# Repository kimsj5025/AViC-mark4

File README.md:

# AViC mark4

이번에는 기존과는 다르게 완전 하이엔드급 보드를 제작해 보려고 하였다. 이를 위해서 TDK사의 가장 최신 센서와 20cm정확도를 갖는 기압 센서, 그리고 내장 GPS와 지자기 센서, 총 4개의 pyro까지, 필요한 모든 것들을 신용카드 사이즈의 보드 안에 통합하려고 하였다.

# 기능 테스트

- [x]  USB 업로드 테스트
- [x]  LED테스트
- [x]  I2C 스캔
- [x]  SDMMC 테스트
- [x]  wifi
- [x]  Pyro 테스트
- [x]  부저
- [x]  GNSS
- [x]  5v out
- [ ]  외부 배터리 연결시 전원 역류방지

## MPU

이번에는 풀 사이즈 Esp32 S3 wroom 1 가 아니라 esp32 s3 mini를 사용하였다.

주요 사양으로는 

- **프로세서:** Xtensa® 32비트 LX7 듀얼 코어 프로세서
- **클럭 주파수:** 최대 240 MHz
- **무선 통신:**
    - 2.4GHz Wi-Fi (802.11 b/g/n)
    - Bluetooth 5 (LE)
- **메모리:**
    - 내부 SRAM: 512KB

주요 사양은 기존의 [AViCDEsp32](https://www.notion.so/AViCDEsp32-20f2a69ddfde80878ec1d9f6c206afdb?pvs=21) 에 사용되었던 MPU와 같은 성능이다.

## 가속도계

가속도계는 TDK InvenSense사의 ICM-45686 6축 가속도 센서를 사용하였다. 이 센서는 최대 32g까지 측정할 수 있으며, 해상도는 16bit이다. 흔히 아두이노용 가속도계로 알려진 mpu6050를 만든 회사의 최신 플래그쉽 가속도 센서이다.

## 기압계

기압계는 MS5607을 사용하였다. 

이 센서의 분해능은 20cm 정도의 높이를 측정할 수 있다. 이 정도면 꽤 정확한 기압계라고 볼 수 있다.

## 자자기계

이번에는 자이로 센서의 드리프트를 보정하기 위해 LIS2MDL 3축 지자기계를 사용하였다.

## GPS

저번 보드에서는 GPS신호를 받으려면 외장 모듈을 활용해야 했지만, 이번에는 ATGM336h과 U.FL 컨넥터로 안테나만 연결해주면 GPS신호를 바로 보드에서 받을 수 있게 하였다.

또한 LED를 연결해 PPS(1초에 한번 신호를 보내는 핀)을 통해 연결 여부를 시각적으로 볼 수 있도록 해 주었다.

## Micro SD카드

저번과 같이 SDMMC를 위한 SD카드 슬롯도 배치하여 주었다.

## 모스펫 스위치

이번에는 4개의 파이로 체널로 구성되었는데. 듀얼 N타입 모스펫이 두개 들어가 있다. 각각의 배선에 따라 최대 4A의 전류를 흐르게 할 수 있다.

## 3.3V, 5V출력

저번과 같이 레귤레이터로는 AMS1117을 사용했다. 다른 점이라면 이번에는 3.3V뿐 아니라 5V도 지원이 된다는 것이다. 이는 추후 사용할 카메라인 Runcam Split 4 4k가 최소 5V 입력을 지원하기에, 이를 보드 내에서 처리하기 위함이다.

## LED 인디케이터

저번 보드에서의 문제점이 이게 작동 중인지 아닌지 관계 없이 전원이 들어오면 LED가 계속 켜져있는다는 것이였는데, 이를 해결하기 위해 MPU에서 직접 이를 조정하게 해 이 문제를 해결했다.

웹에서 센서 데이터를 읽어올 때 마다 LED가 깜빡이게 만든 모습

## 부저

이 는 원래 에이비오닉스로 활용될 계획도 갖고 있어서, 로켓 내부에 있을 때에 청각적으로 작동중임을 알 수 있도록 부저를 달아서 알 수 있게 하였다.

또한 부팅시에 부팅음을 넣어서 시리얼 모니터를 보지 않아도 정상적으로 리셋이 되었는지 알 수 있도록 하였다.

## USB-C

ESP32 s3는 풀 스피드 USB2.0를 지원하고 내장 CDC가 있기 때문에 D- D+핀만 정상적으로 연결해 준다면 usb를 이용하여 코딩과 시리얼 모니터(UART0)를 볼 수 있다. 또한 USB에서 나오는 5V전원을 통해 보드 전체의 전원이 들어올 수 있도록 해 주었다. 이를 통해 기존 코드 업로드 방식에서 엄청난 혁신을 이루었는데, 코드를 업로드 할 때마다 리셋 버튼을 누르는 수고와 항상 USB TTL컨버터를 찾아야 하는 번거로움에서 해방되었다. (그래서 USB TTL컨버터를 잃어버렸다;)

또한 이 USB-C에 대한 글을 하나 작성하였다. 

https://kimsj5025.tistory.com/entry/Esp32-S3-USB-OTG-%EC%8B%9C%EB%A6%AC%EC%96%BC-%EB%AA%A8%EB%8B%88%ED%84%B0%EA%B0%80-%EC%95%88%EB%82%98%EC%98%AC%EB%95%8C-%ED%95%B4%EA%B2%B0-%EB%B0%A9%EB%B2%95-ArduinoIDE-PlatformIO

## 더 많은 GPIO

PWM용, UART 통신(+ RX TX -)을 위한 헤더핀 총 8개 그리고 3.3,5V 각각 두개, 4개의 파이로 체널, 9개의 GPIO, 3개의 GND 총 20개의 터미널 블럭을 이용한 단자를 만들어 주었다. 또한 각가그이 M4 나사 규격의 마운트홀도 모두 GND에 연결해 주어 총 7개의 GND단자가 있게 되었다.

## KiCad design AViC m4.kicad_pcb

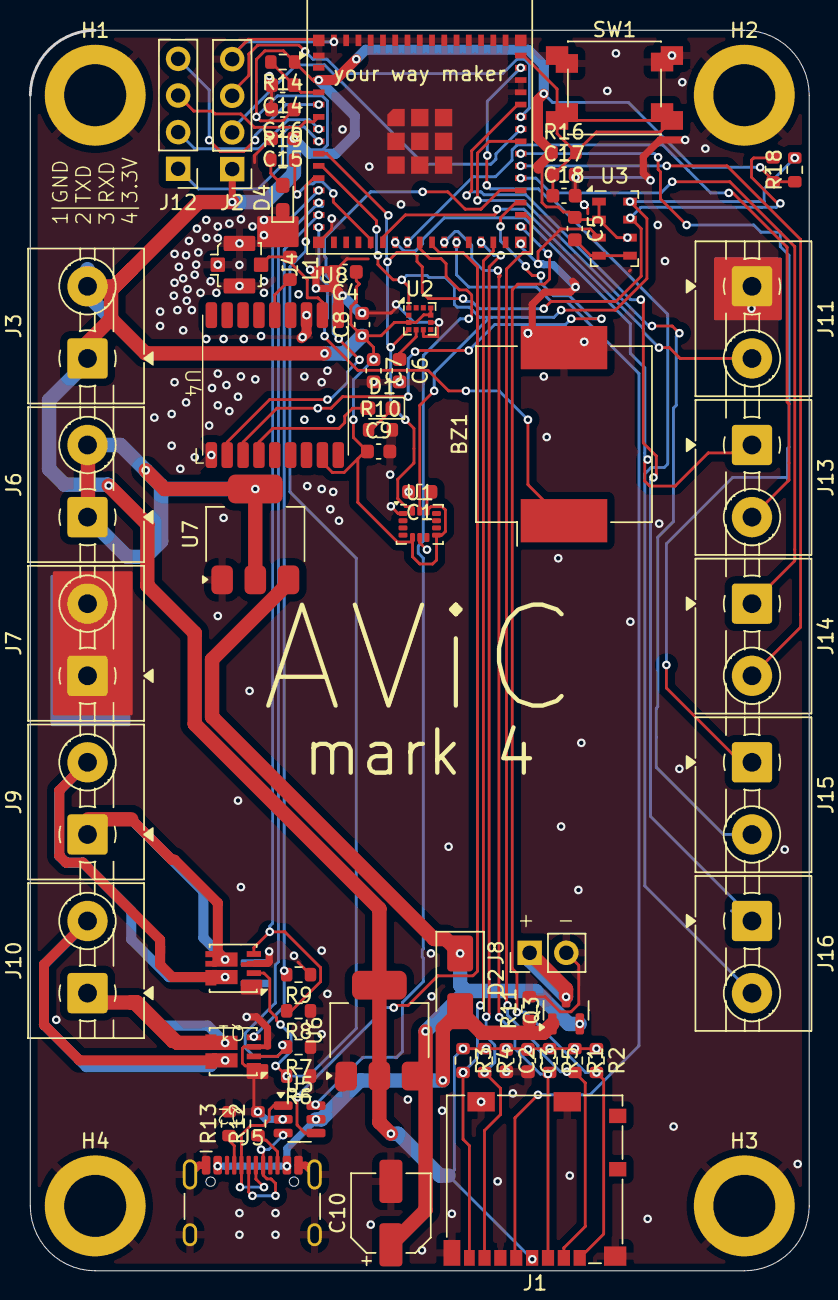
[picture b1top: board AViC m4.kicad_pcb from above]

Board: 2 copper layers, 54.0 x 86.0 mm, 70 parts (0 on the bottom side), 56 nets.

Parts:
BZ1: Buzzer; Buzzer_Mallory_AST1240MLQ
C1, C2, C4, C5, C7, C9, C16: 10uF; C_0603_1608Metric
C3, C8, C14, C15, C17: 0.1uF; C_0603_1608Metric
C6: 220nF; C_0603_1608Metric
C10: 47uF; CP_Elec_5x5.4
C18: 1uF; C_0603_1608Metric
D1: RED; LED_0603_1608Metric_Pad1.05x0.95mm_HandSolder
D2: SS14; D_SMA
D4: LED; LED_0603_1608Metric_Pad1.05x0.95mm_HandSolder
H1, H2, H3, H4: m4; MountingHole_4.3mm_M4_ISO14580_Pad
J1: Micro_SD_Card_Det_Hirose_DM3AT; microSD_HC_Molex_104031-0811
J2: Lora; PinHeader_1x04_P2.54mm_Vertical
J3, J6, J7, J9, J10: Power ternimal LEFT; TerminalBlock_MaiXu_MX126-5.0-02P_1x02_P5.00mm
J4: Conn_Coaxial; U.FL_Molex_MCRF_73412-0110_Vertical
J5: USB_C_Receptacle_USB2.0_16P; USB_C_Receptacle_HCTL_HC-TYPE-C-16P-01A
J8: Batt; PinHeader_1x02_P2.54mm_Vertical
J11, J13, J14, J15, J16: GPIOs; TerminalBlock_MaiXu_MX126-5.0-02P_1x02_P5.00mm
J12: PWM; PinHeader_1x04_P2.54mm_Vertical
L1: 27n; L_0603_1608Metric
Q1, Q2: SI7232DN-T1-GE3; mosfet_custom
Q3: DMG2302U; SOT-23
R1, R2, R3, R4, R5, R14, R16, R17, R18: 10k; R_0603_1608Metric
R6, R7, R8, R9: 4.7k; R_0603_1608Metric
R10: 1KR; R_0603_1608Metric
R11: 100k; R_0603_1608Metric
R12, R13: 5k1; R_0603_1608Metric
R19: 330; R_0603_1608Metric
SW1: Flash Mode; SW_SPST_PTS645
U1: ICM-45686; LGA-14_3x2.5mm_P0.5mm_LayoutBorder3x4y
U2: LIS2MDL; LGA-12_2x2mm_P0.5mm
U3: MS5607-02BA; LGA-8_3x5mm_P1.25mm
U4: ATGM336h
U5: USBLC6-2SC6; SOT-23-6
U6: AMS1117-3.3; SOT-223-3_TabPin2
U7: AMS1117-5.0; SOT-223-3_TabPin2
U8: ESP32-S3-MINI-1; ESP32-S2-MINI-1

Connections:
+3.3V: C1.1, C2.1, C3.1, C4.1, C5.1, C7.1, C8.1, C9.1, C15.1, C16.1, J1.4 (VDD), J2.1, J3.1, J3.2, R1.1, R2.1, R3.1, R4.1, R5.1, R14.1, R16.1, R17.1, R18.1, U1.5 (VDDIO), U1.8 (VDD), U1.12 (AP_CS), U2.3 (~CS), U2.9 (Vdd), U2.10 (Vdd_IO), U3.1 (VDD), U3.2 (PS), U3.6 (SDO), U4.8 (VCC), U6.2 (VO), U8.3 (3V3)
+5V: J6.1, J6.2, U7.2 (VO)
+BATT: J8.1, Q3.3 (D)
/MCU/FLASH: C14.1, R14.2, U8.4 (IO0)
/MCU/LED: R19.2, U8.19 (IO15)
/MCU/PWM 1: J12.4, U8.5 (IO1)
/MCU/PWM 2: J12.3, U8.6 (IO2)
/MCU/PWM 3: J12.2, U8.7 (IO3)
/MCU/PWM 4: J12.1, U8.8 (IO4)
/MCU/RESET: C17.1, C18.1, R16.2, SW1.2, U8.45 (EN)
/MCU/UART0_RXD: J2.3, U8.40 (RXD0)
/MCU/UART0_TXD: J2.2, U8.39 (TXD0)
/functions/1PPS: D1.2 (A), U4.4 (1PPS)
/functions/GPS_ANT: J4.1 (In), L1.1, U4.11 (RF_IN)
/functions/SW1: J9.1, Q1.7
/functions/SW2: J9.2, Q1.6
/functions/SW3: J10.1, Q2.7
/functions/SW4: J10.2, Q2.6
/functions/VCC_RF: L1.2, U4.14 (VCC_RF)
BUZZER: BZ1.1 (+), U8.15 (IO11)
CLK: J1.5 (CLK), U8.26 (IO26)
CMD: J1.3 (CMD), R5.2, U8.25 (IO21)
D+: U5.4 (I/O2), U8.24 (USB_D+)
D-: U5.6 (I/O1), U8.23 (USB_D-)
DAT0: J1.7 (DAT0), R4.2, U8.28 (IO33)
DAT1: J1.8 (DAT1), R3.2, U8.29 (IO34)
DAT2: J1.1 (DAT2), R2.2, U8.31 (IO35)
DAT3: J1.2 (DAT3/CD), R1.2, U8.32 (IO36)
GND: BZ1.2 (-), C1.2, C2.2, C3.2, C4.2, C6.2, C7.2, C8.2, C9.2, C10.2, C14.2, C15.2, C16.2, C17.2, C18.2, D4.1 (K), H1.1, H2.1, H3.1, H4.1, J1.6 (VSS), J1.11 (SHIELD), J2.4, J4.2 (Ext), J5.A1 (GND), J5.A12 (GND), J5.B1 (GND), J5.B12 (GND), J5.S1 (SHIELD), J7.1, J7.2, J8.2, J11.1, Q1.1, Q1.3, Q2.1, Q2.3, R6.1, R7.1, R8.1, R9.1, R10.2, R11.2, R12.2, R13.2, SW1.1, U1.1 (AP_SDO/AP_AD0), U1.6 (GND), U2.6 (GND), U2.8 (GND), U3.3 (GND), U4.1 (GND), U4.10 (GND), U4.12 (GND), U5.2 (GND), U6.1 (GND), U7.1 (GND), U8.1 (GND), U8.2 (GND), U8.42 (GND), U8.43 (GND), U8.46 (GND), U8.47 (GND), U8.48 (GND), U8.49 (GND), U8.50 (GND), U8.51 (GND), U8.52 (GND), U8.53 (GND), U8.54 (GND), U8.55 (GND), U8.56 (GND), U8.57 (GND), U8.58 (GND), U8.59 (GND), U8.60 (GND), U8.61 (GND), U8.62 (GND), U8.63 (GND), U8.64 (GND), U8.65 (GND)
GPIO16: J11.2, U8.20 (IO16)
GPIO17: J13.1, U8.21 (IO17)
GPIO18: J13.2, U8.22 (IO18)
GPS RX: U4.3 (RD), U8.33 (IO37)
GPS TX: U4.2 (TX), U8.34 (IO38)
unnamed: C5.2, U3.4 (CSB), U3.5 (CSB)
unnamed: D1.1 (K), R10.1
unnamed: C10.1, D2.1 (K), Q3.2 (S), U6.3 (VI), U7.3 (VI)
unnamed: D4.2 (A), R19.1
unnamed: J5.A5 (CC1), R13.1
unnamed: J5.B5 (CC2), R12.1
unnamed: J5.A6 (D+), J5.B6 (D+), U5.3 (I/O2)
unnamed: J5.A7 (D-), J5.B7 (D-), U5.1 (I/O1)
unnamed: J14.1, U8.35 (IO39)
unnamed: J14.2, U8.36 (IO40)
unnamed: J15.1, U8.37 (IO41)
unnamed: J15.2, U8.38 (IO42)
unnamed: J16.1, U8.41 (IO45)
unnamed: J16.2, U8.44 (IO46)
unnamed: C6.1, U2.5 (C1)
SCL: R18.2, U1.13 (AP_SCL/AP_SCLK), U2.1 (SCL/SPC), U3.8 (SCLK), U8.10 (IO6)
SDA: R17.2, U1.14 (AP_SDA/AP_SDIO/AP_SDI), U2.4 (SDA/SDI/SDO), U3.7 (SDI/SDA), U8.9 (IO5)
SW1 control: Q1.2, R6.2, U8.11 (IO7)
SW2 control: Q1.4, R8.2, U8.12 (IO8)
SW3 control: Q2.2, R7.2, U8.13 (IO9)
SW4 control: Q2.4, R9.2, U8.14 (IO10)
VBUS: D2.2 (A), J5.A4 (VBUS), J5.A9 (VBUS), J5.B4 (VBUS), J5.B9 (VBUS), Q3.1 (G), R11.1, U5.5 (VBUS)

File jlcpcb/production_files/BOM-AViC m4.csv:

Comment,Designator,Footprint,LCSC,Quantity
27n,L1,L_0603_1608Metric,C12100,1
SI7232DN-T1-GE3,"Q1,Q2",mosfet_custom,C144854,2
0.1uF,"C14,C15,C17,C3,C8",C_0603_1608Metric,C14663,5
1uF,C18,C_0603_1608Metric,C15849,1
USB_C_Receptacle_USB2.0_16P,J5,USB_C_Receptacle_HCTL_HC-TYPE-C-16P-01A,C165948,1
10uF,C9,C_0603_1608Metric,C19702,1
220nF,C6,C_0603_1608Metric,C21120,1
1KR,R10,R_0603_1608Metric,C21190,1
RED,"D1,D4",LED_0603_1608Metric_Pad1.05x0.95mm_HandSolder,C2286,2
330,R19,R_0603_1608Metric,C23138,1
4.7k,"R6,R7,R8,R9",R_0603_1608Metric,C23162,4
5k1,"R12,R13",R_0603_1608Metric,C23186,2
100k,R11,R_0603_1608Metric,C25803,1
10k,"R1,R14,R16,R17,R18,R2,R3,R4,R5",R_0603_1608Metric,C25804,9
ESP32-S3-MINI-1,U8,ESP32-S2-MINI-1,C2913206,1
Flash Mode,SW1,SW_SPST_PTS645,C318884,1
47uF,C10,CP_Elec_5x5.4,C3337,1
Power ternimal LEFT,"J10,J11,J13,J14,J15,J16,J3,J6,J7,J9",TerminalBlock_MaiXu_MX126-5.0-02P_1x02_P5.00mm,C430623,10
Conn_Coaxial,J4,U.FL_Molex_MCRF_73412-0110_Vertical,C5137195,1
Micro_SD_Card_Det_Hirose_DM3AT,J1,microSD_HC_Molex_104031-0811,C585350,1
Buzzer,BZ1,Buzzer_Mallory_AST1240MLQ,C7421651,1
~,U4,ATGM336h,C90770,1
10uF,"C1,C16,C2,C4,C5,C7",C_0603_1608Metric,C96446,6
MS5607-02BA,U3,LGA-8_3x5mm_P1.25mm,C97627,1
PWM,J12,PinHeader_1x04_P2.54mm_Vertical,,1
Lora,J2,PinHeader_1x04_P2.54mm_Vertical,,1
SS14,D2,D_SMA,,1
USBLC6-2SC6,U5,SOT-23-6,,1
LIS2MDL,U2,LGA-12_2x2mm_P0.5mm,,1
AMS1117-3.3,U6,SOT-223-3_TabPin2,,1
ICM-45686,U1,LGA-14_3x2.5mm_P0.5mm_LayoutBorder3x4y,,1
AMS1117-5.0,U7,SOT-223-3_TabPin2,,1
Batt,J8,PinHeader_1x02_P2.54mm_Vertical,,1
DMG2302U,Q3,SOT-23,,1

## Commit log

2025-07-23 first
2025-07-23 README.MD (notion ver)
    노션에 써 놓은 것을 Export해서 올려봅니다.
    사진도 같이 올라갈진 모르겠음
2025-07-23 to-do list 하나 삭제
2025-07-23 adding image
